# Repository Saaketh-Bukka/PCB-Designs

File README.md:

# PCB-Design

This repository lists all PCB Designs made and used for engineering projects.

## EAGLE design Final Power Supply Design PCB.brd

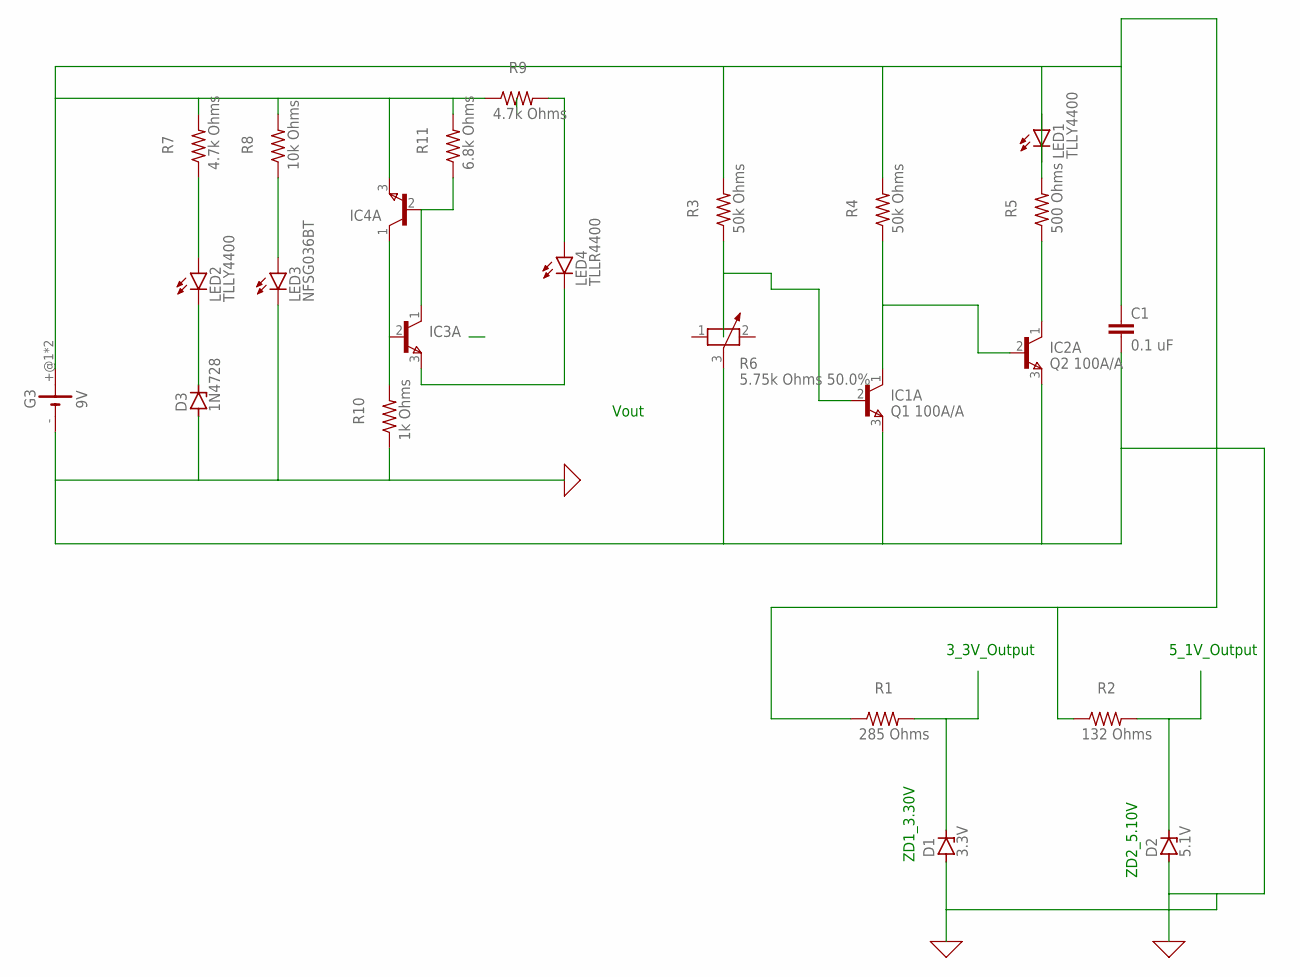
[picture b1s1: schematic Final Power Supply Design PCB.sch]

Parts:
C1: 0.1 uF; C2.5-4
D1: 3.3V; DO41Z10
D2: 5.1V; DO41Z10
D3: 1N4728; DO41Z10
G3: 9V; 10MM_SM_COIN_CELL_CLIP
IC1: Q1 100A/A; TO78
IC2: Q2 100A/A; TO78
IC3, IC4: MAT-01H; TO78
LED1, LED2: TLLY4400; LED3MM
LED3: NFSG036BT
LED4: TLLR4400; LED3MM
R1: 285 Ohms; 0204V
R2: 132 Ohms; 0204V
R3, R4: 50k Ohms; 0204V
R5: 500 Ohms; 0204V
R6: 5.75k Ohms 50.0%; PT-10
R7, R9: 4.7k Ohms; 0204V
R8: 10k Ohms; 0204V
R10: 1k Ohms; 0204V
R11: 6.8k Ohms; 0204V

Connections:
0: C1.2, D1.A, D2.A, D3.A, G3.-, IC1.3 (E), IC2.3 (E), LED3.C, R6.3, R10.1
unnamed: D2.C, R2.2
unnamed: C1.1, G3.+@1 (+), G3.+@2 (+), IC4.3 (E), LED1.A, LED1.K (C), R1.1, R2.1, R3.2, R4.2, R5.2, R7.2, R8.2, R9.1, R11.2
unnamed: IC1.2 (B), R3.1
unnamed: IC1.1 (C), IC2.2 (B), R4.1
unnamed: IC2.1 (C), R5.1
unnamed: LED2.A, R7.1
unnamed: LED3.A, R8.1
unnamed: D3.C, LED2.K (C)
unnamed: LED4.A, R9.2
unnamed: IC3.2 (B), IC4.1 (C), R10.2
unnamed: IC3.1 (C), IC4.2 (B), R11.1
unnamed: IC3.3 (E), LED4.K (C)
unnamed: D1.C, R1.2

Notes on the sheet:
Vout
5_1V_Output
3_3V_Output
ZD1_3.30V
ZD2_5.10V

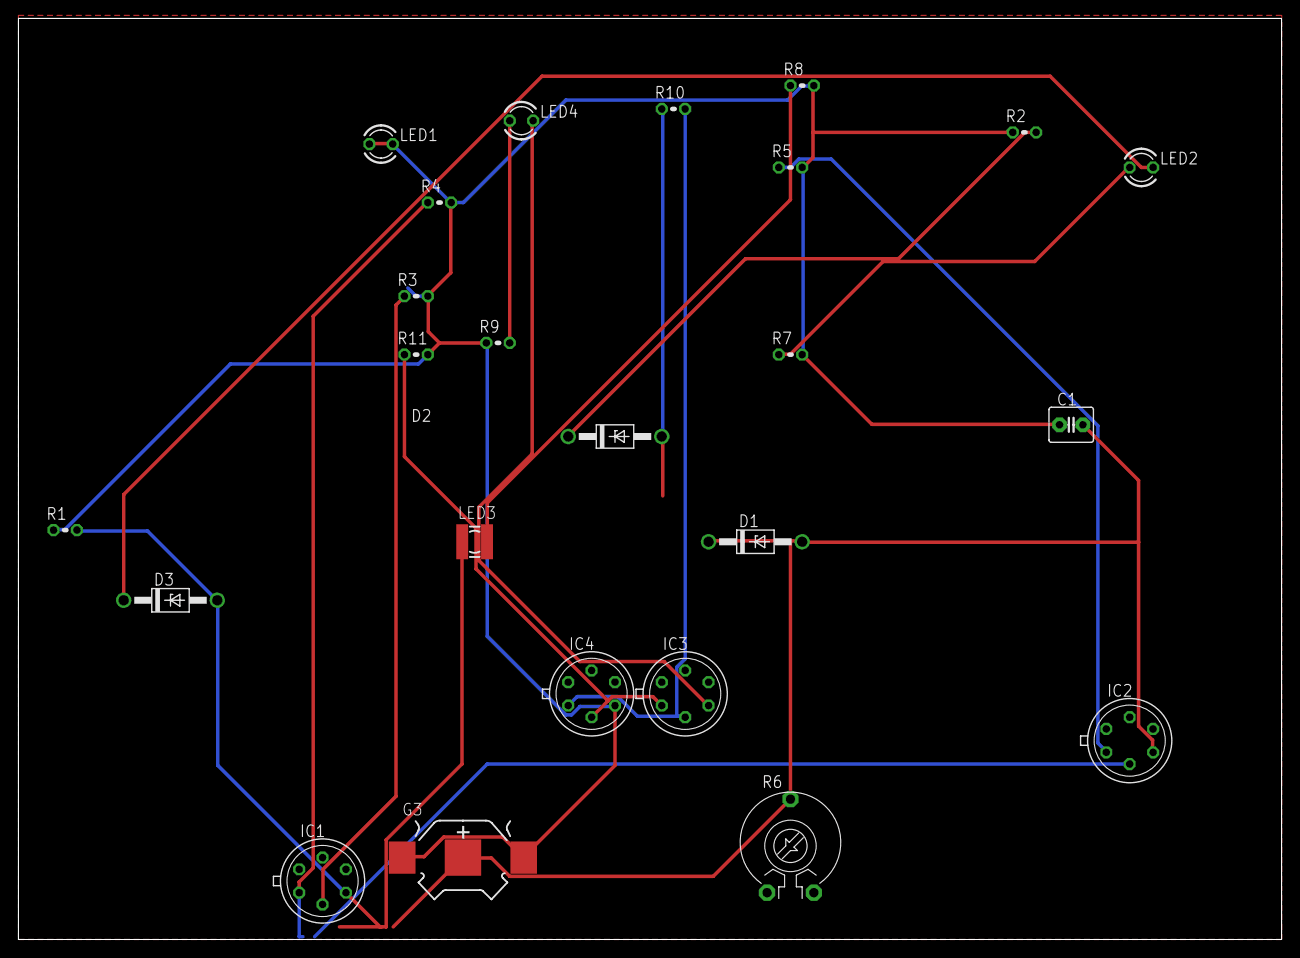
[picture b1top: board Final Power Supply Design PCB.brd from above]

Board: 2 copper layers, 137.1 x 100.0 mm, 24 parts (0 on the bottom side), 14 nets.
